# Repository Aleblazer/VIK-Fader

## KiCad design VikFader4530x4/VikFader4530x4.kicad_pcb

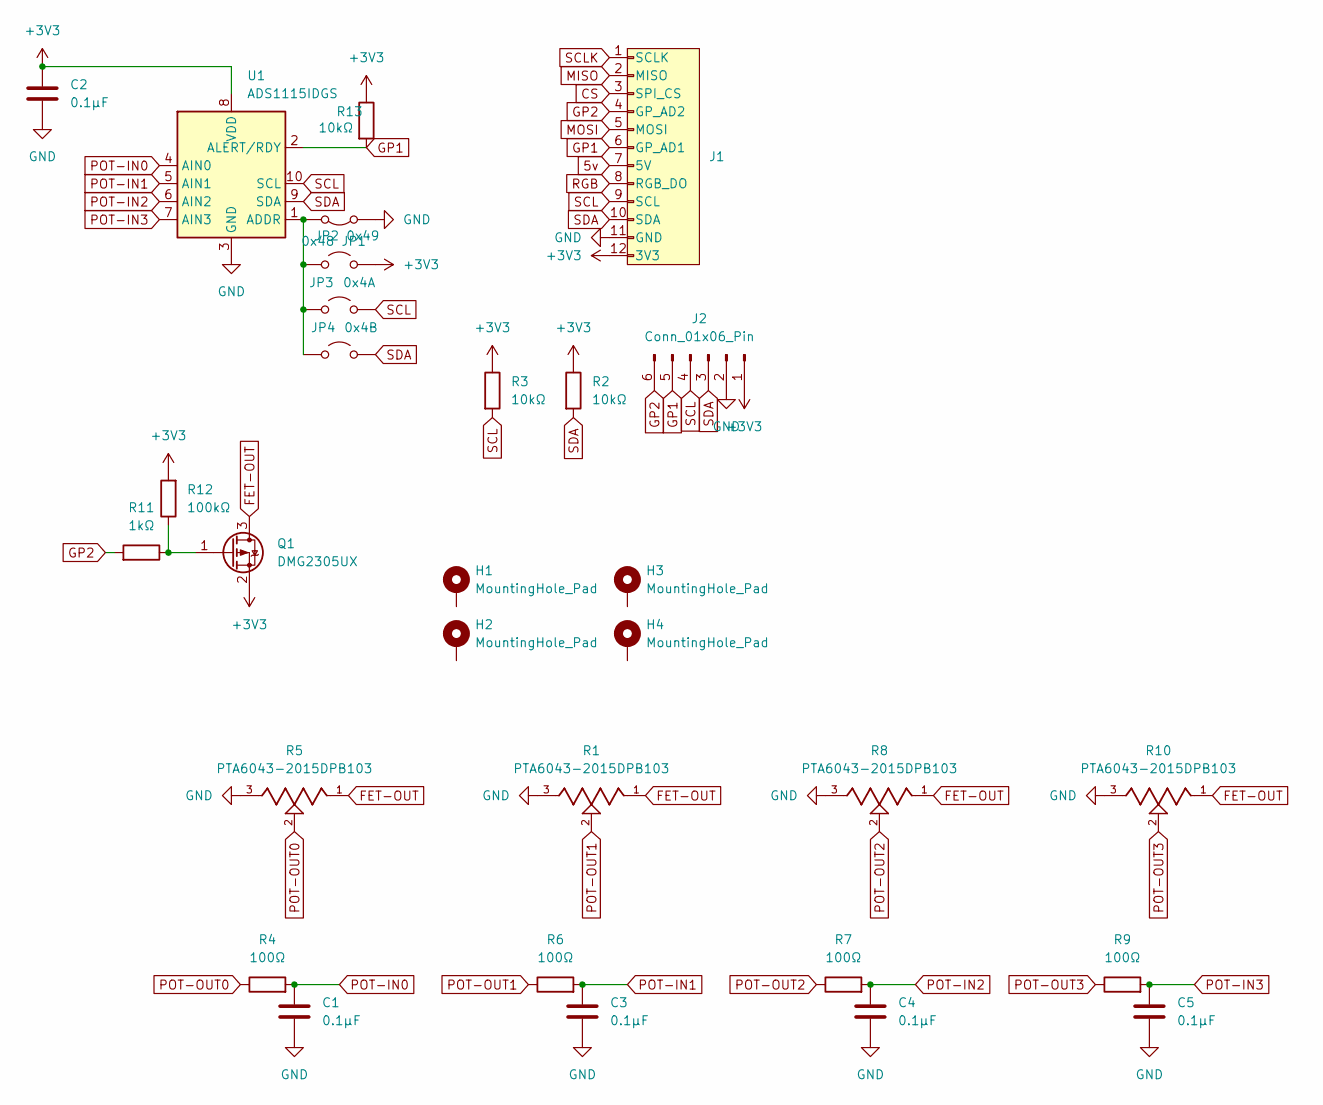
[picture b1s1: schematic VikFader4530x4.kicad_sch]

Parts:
C1, C2, C3, C4, C5: 0.1µF; C_0603_1608Metric
H1, H2, H3, H4: MountingHole_Pad; SMD_BD5.6-L5.6-W5.6-D4.1
J1: vik-module-connector; vik-module-connector-horizontal
J2: Conn_01x06_Pin; PinHeader_1x06_P2.54mm_Vertical
JP1: 0x48; SolderJumper-2_P1.3mm_Bridged_RoundedPad1.0x1.5mm
JP2: 0x49; SolderJumper-2_P1.3mm_Open_RoundedPad1.0x1.5mm
JP3: 0x4A; SolderJumper-2_P1.3mm_Open_RoundedPad1.0x1.5mm
JP4: 0x4B; SolderJumper-2_P1.3mm_Open_RoundedPad1.0x1.5mm
Q1: DMG2305UX; SOT-23
R1, R5, R8, R10: PTA6043-2015DPB103; TRIM_PTA3043-2010CPB103; PARTREV 08/25
R2, R3, R13: 10kΩ; R_0805_2012Metric
R4, R6, R7, R9: 100Ω; C_0603_1608Metric
R11: 1kΩ; R_0603_1608Metric
R12: 100kΩ; R_0603_1608Metric
U1: ADS1115IDGS; TSSOP-10_3x3mm_P0.5mm

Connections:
5v: J1.7 (5V)
+3V3: C2.1, J1.12 (3V3), J2.1, JP2.2 (B), Q1.2 (S), R2.1, R3.1, R12.2, R13.1, U1.8 (VDD)
CS: J1.3 (SPI_CS)
FET-OUT: Q1.3 (D), R1.1, R5.1, R8.1, R10.1
GND: C1.2, C2.2, C3.2, C4.2, C5.2, J1.11 (GND), J2.2, JP1.1 (A), R1.3, R5.3, R8.3, R10.3, U1.3 (GND)
GP1: J1.6 (GP_AD1), J2.5, R13.2, U1.2 (ALERT/RDY)
GP2: J1.4 (GP_AD2), J2.6, R11.2
MISO: J1.2 (MISO)
MOSI: J1.5 (MOSI)
unnamed: JP1.2 (B), JP2.1 (A), JP3.1 (A), JP4.1 (A), U1.1 (ADDR)
unnamed: Q1.1 (G), R11.1, R12.1
POT-IN0: C1.1, R4.2, U1.4 (AIN0)
POT-IN1: C3.1, R6.2, U1.5 (AIN1)
POT-IN2: C4.1, R7.2, U1.6 (AIN2)
POT-IN3: C5.1, R9.2, U1.7 (AIN3)
POT-OUT0: R4.1, R5.2
POT-OUT1: R1.2, R6.1
POT-OUT2: R7.1, R8.2
POT-OUT3: R9.1, R10.2
RGB: J1.8 (RGB_DO)
SCL: J1.9 (SCL), J2.4, JP3.2 (B), R3.2, U1.10 (SCL)
SCLK: J1.1 (SCLK)
SDA: J1.10 (SDA), J2.3, JP4.2 (B), R2.2, U1.9 (SDA)

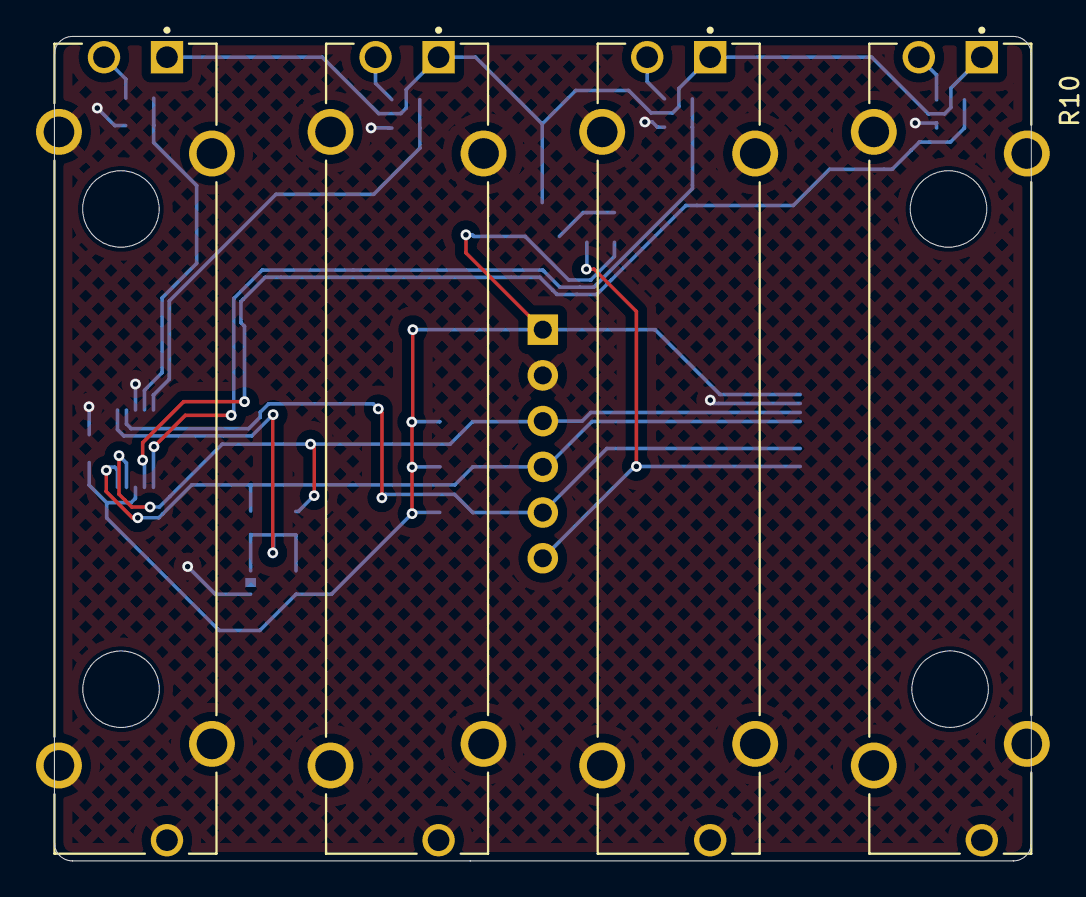
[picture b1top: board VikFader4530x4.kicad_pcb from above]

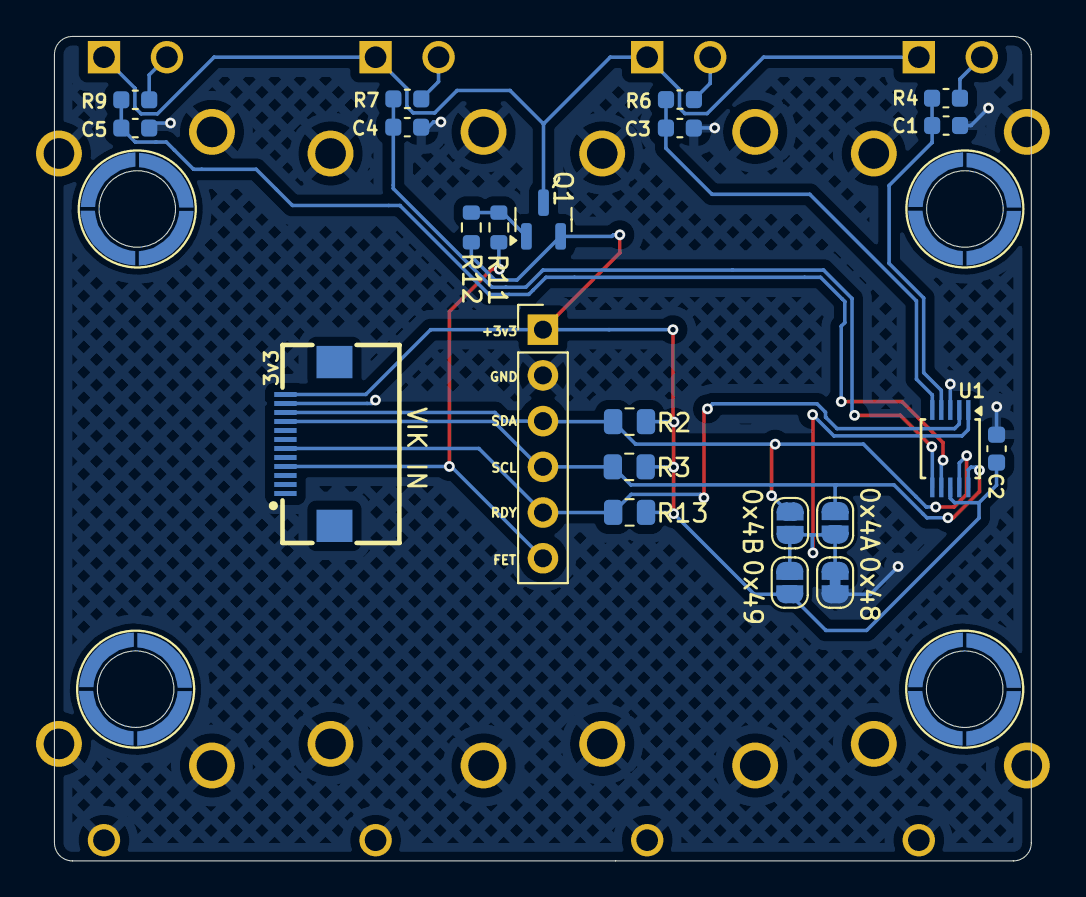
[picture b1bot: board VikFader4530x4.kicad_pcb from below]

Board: 2 copper layers, 54.3 x 45.8 mm, 30 parts (26 on the bottom side), 17 nets.

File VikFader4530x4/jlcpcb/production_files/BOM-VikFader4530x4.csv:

Comment,Designator,Footprint,LCSC,Quantity
0.1µF,"C1,C2,C3,C4,C5",C_0603_1608Metric,C14663,5
100kΩ,R12,R_0603_1608Metric,C25803,1
100Ω,"R4,R6,R7,R9",C_0603_1608Metric,C22775,4
10kΩ,"R13,R2,R3",R_0805_2012Metric,C17414,3
1kΩ,R11,R_0603_1608Metric,C21190,1
ADS1115IDGS,U1,TSSOP-10_3x3mm_P0.5mm,C37593,1
DMG2305UX,Q1,SOT-23,C2940629,1
vik-module-connector,J1,vik-module-connector-horizontal,C2906115,1

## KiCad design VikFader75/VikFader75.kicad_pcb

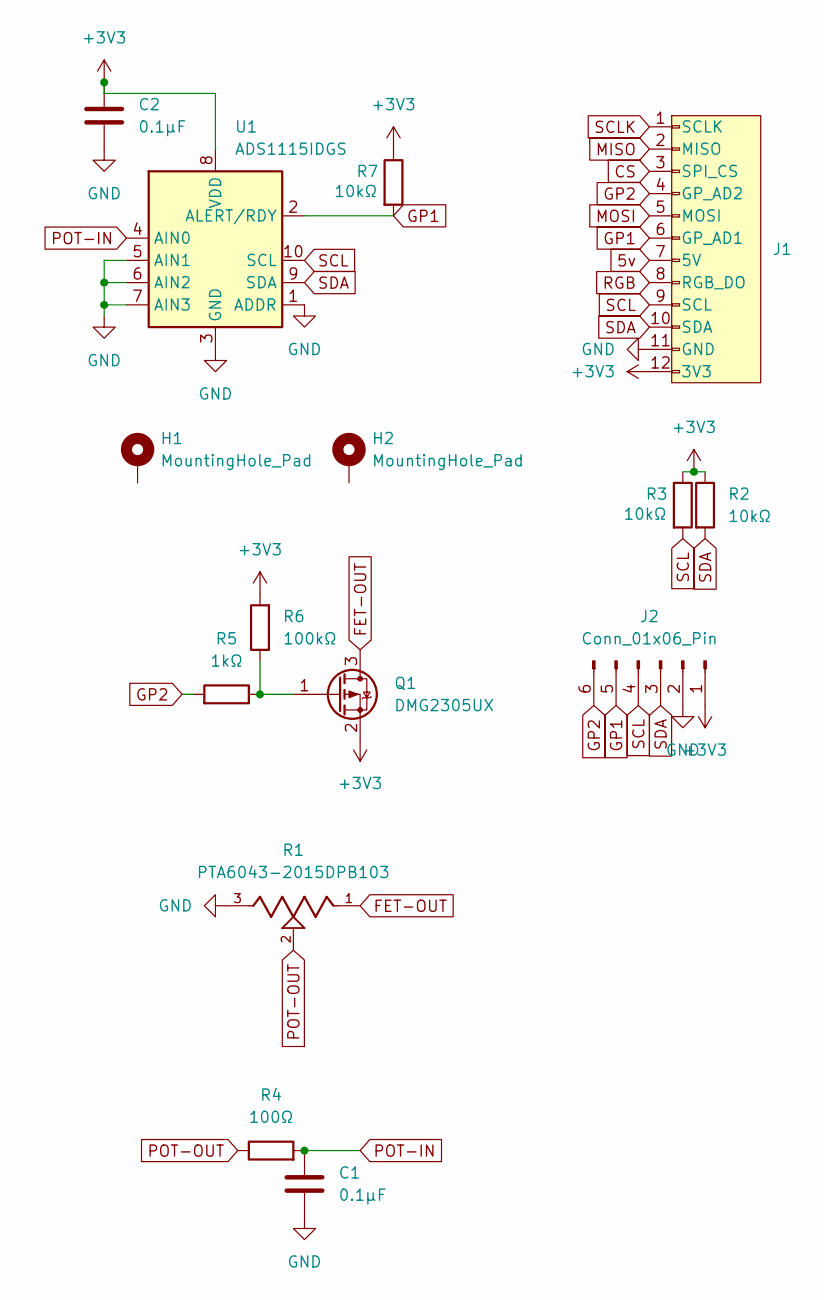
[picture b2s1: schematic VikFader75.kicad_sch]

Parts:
C1, C2: 0.1µF; C_0603_1608Metric
H1, H2: MountingHole_Pad; SMD_BD5.6-L5.6-W5.6-D4.1
J1: vik-module-connector; vik-module-connector-horizontal
J2: Conn_01x06_Pin; PinHeader_1x06_P2.54mm_Vertical
Q1: DMG2305UX; SOT-23
R1: PTA6043-2015DPB103; TRIM_PTA6043-2015DPB103; PARTREV 08/25
R2, R3, R7: 10kΩ; R_0805_2012Metric
R4: 100Ω; R_0603_1608Metric
R5: 1kΩ; R_0603_1608Metric
R6: 100kΩ; R_0603_1608Metric
U1: ADS1115IDGS; TSSOP-10_3x3mm_P0.5mm

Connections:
5v: J1.7 (5V)
+3V3: C2.1, J1.12 (3V3), J2.1, Q1.2 (S), R2.1, R3.1, R6.2, R7.1, U1.8 (VDD)
CS: J1.3 (SPI_CS)
FET-OUT: Q1.3 (D), R1.1
GND: C1.2, C2.2, J1.11 (GND), J2.2, R1.3, U1.1 (ADDR), U1.3 (GND), U1.5 (AIN1), U1.6 (AIN2), U1.7 (AIN3)
GP1: J1.6 (GP_AD1), J2.5, R7.2, U1.2 (ALERT/RDY)
GP2: J1.4 (GP_AD2), J2.6, R5.2
MISO: J1.2 (MISO)
MOSI: J1.5 (MOSI)
unnamed: Q1.1 (G), R5.1, R6.1
POT-IN: C1.1, R4.2, U1.4 (AIN0)
POT-OUT: R1.2, R4.1
RGB: J1.8 (RGB_DO)
SCL: J1.9 (SCL), J2.4, R3.2, U1.10 (SCL)
SCLK: J1.1 (SCLK)
SDA: J1.10 (SDA), J2.3, R2.2, U1.9 (SDA)

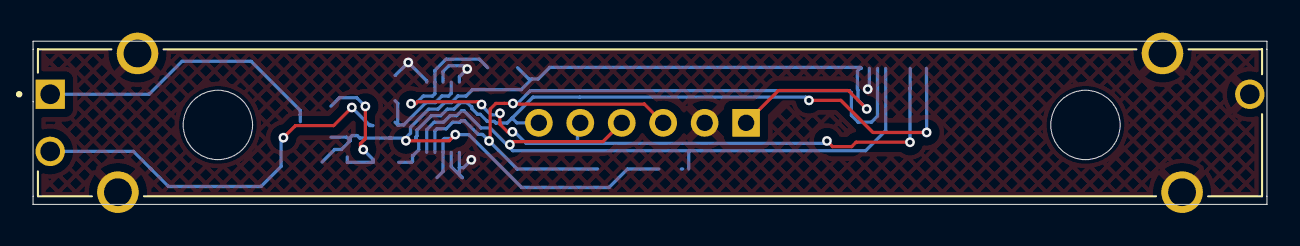
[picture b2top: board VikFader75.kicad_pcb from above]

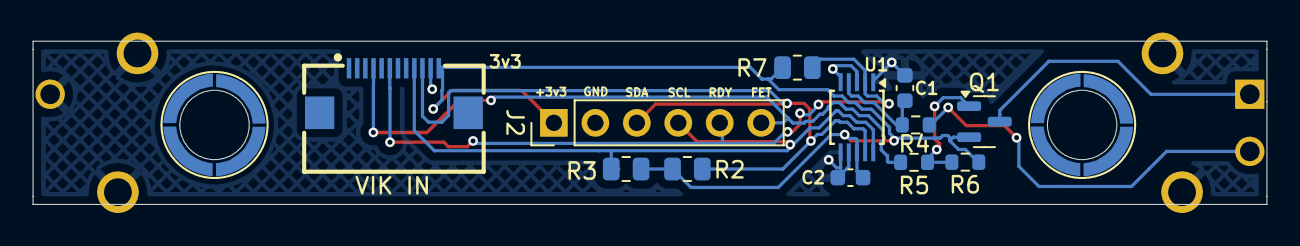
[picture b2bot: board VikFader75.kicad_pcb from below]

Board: 2 copper layers, 75.6 x 10.0 mm, 15 parts (14 on the bottom side), 10 nets.

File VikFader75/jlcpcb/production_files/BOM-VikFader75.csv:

Comment,Designator,Footprint,LCSC,Quantity
0.1µF,"C1,C2",C_0603_1608Metric,C14663,2
100kΩ,R6,R_0603_1608Metric,C25803,1
100Ω,R4,R_0603_1608Metric,C22775,1
10kΩ,"R2,R3,R7",R_0805_2012Metric,C17414,3
1kΩ,R5,R_0603_1608Metric,C21190,1
ADS1115IDGS,U1,TSSOP-10_3x3mm_P0.5mm,C37593,1
DMG2305UX,Q1,SOT-23,C2940629,1
vik-module-connector,J1,vik-module-connector-horizontal,C2906115,1
